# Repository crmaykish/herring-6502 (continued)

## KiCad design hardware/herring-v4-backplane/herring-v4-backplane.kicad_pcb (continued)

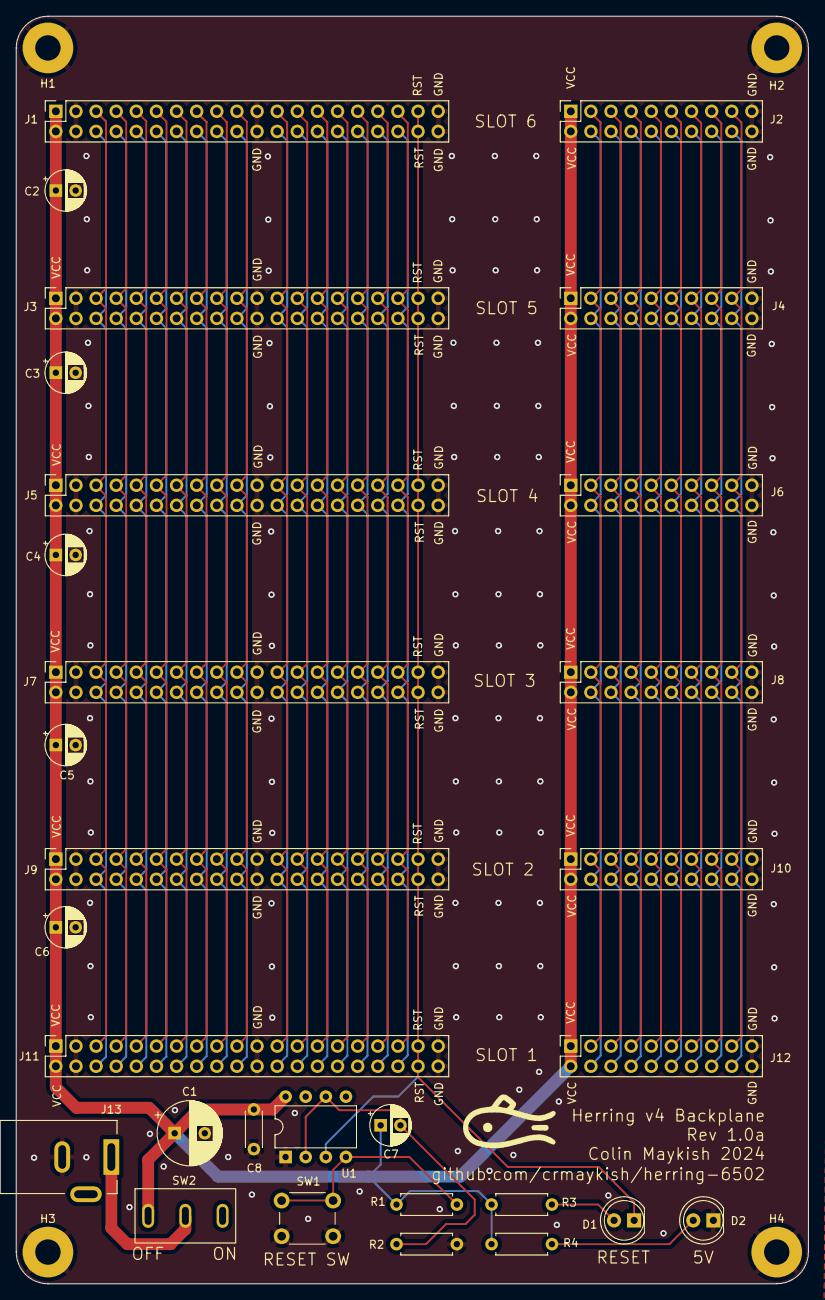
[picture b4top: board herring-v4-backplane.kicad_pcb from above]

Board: 2 copper layers, 100.0 x 160.0 mm, 34 parts (0 on the bottom side), 54 nets.

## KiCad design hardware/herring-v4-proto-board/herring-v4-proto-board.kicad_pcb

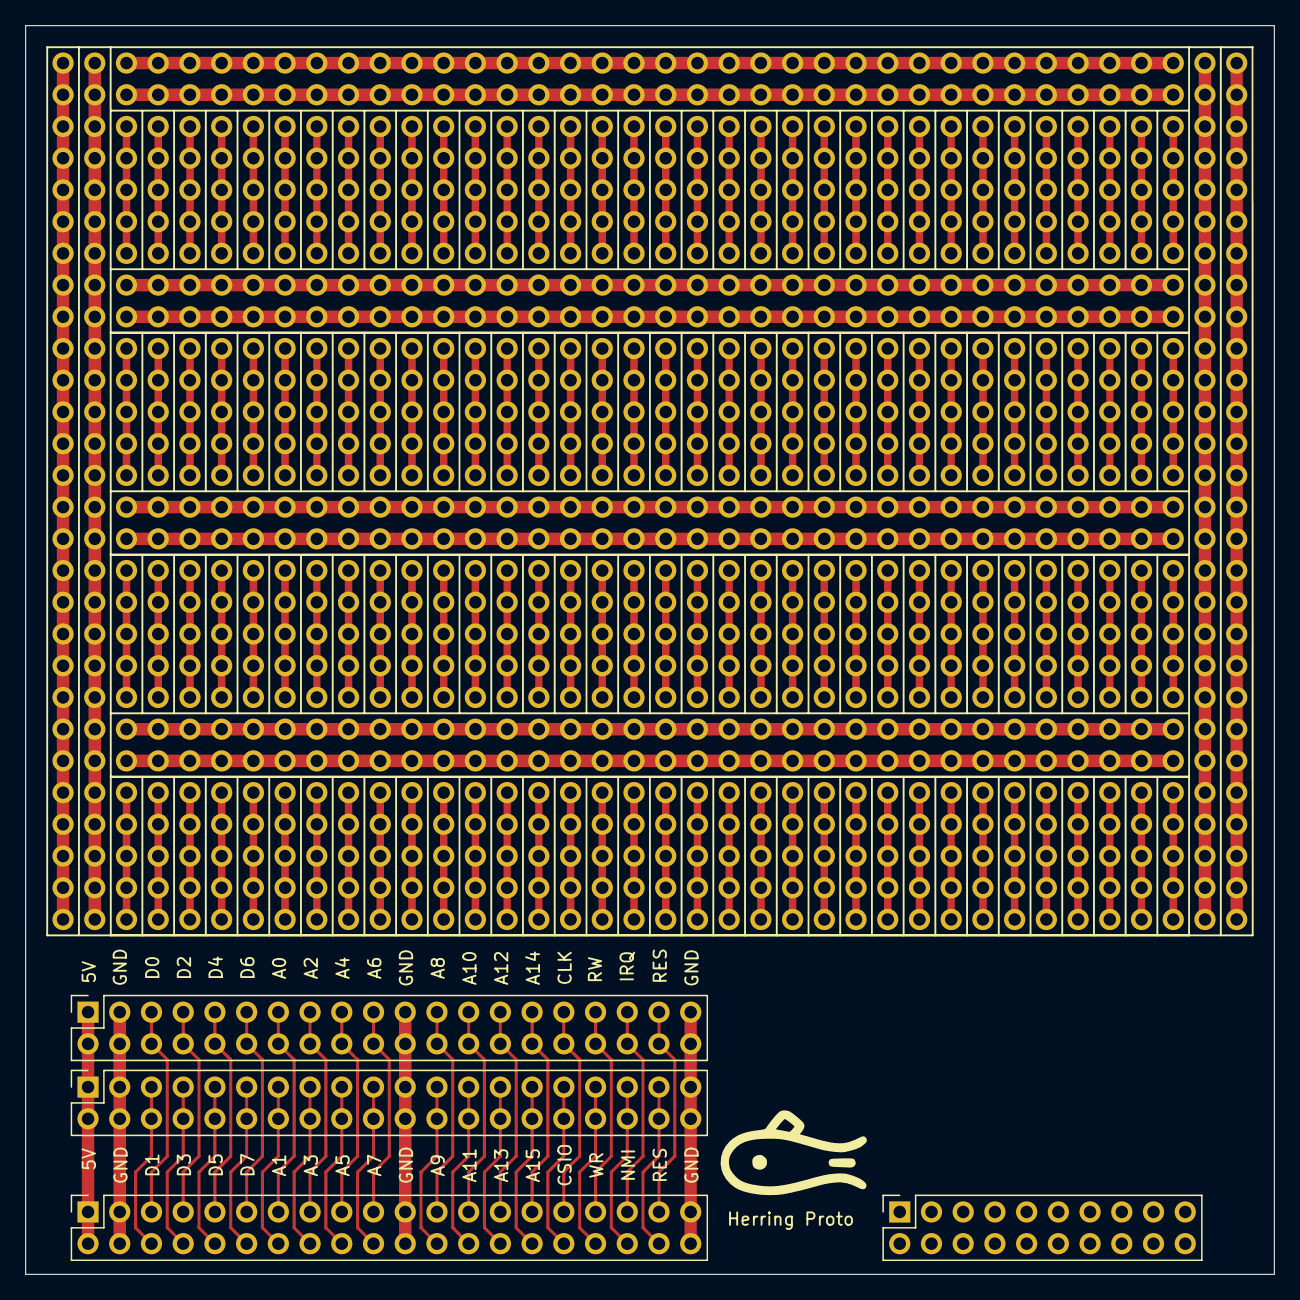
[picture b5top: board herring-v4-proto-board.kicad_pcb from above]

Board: 2 copper layers, 100.0 x 100.0 mm, 4 parts (0 on the bottom side), 33 nets.

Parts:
J1, J4, J5: Conn_02x20_Odd_Even; PinSocket_2x20_P2.54mm_Vertical
J2: Conn_02x10_Odd_Even; PinSocket_2x10_P2.54mm_Vertical

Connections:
+5V: J1.1, J1.2, J4.1, J4.2, J5.1, J5.2
/A0: J1.13, J5.13, J5.14
/A1: J1.14, J4.13, J4.14
/A2: J1.15, J5.15, J5.16
/A3: J1.16, J4.15, J4.16
/A4: J1.17, J5.17, J5.18
/A5: J1.18, J4.17, J4.18
/A6: J1.19, J5.19, J5.20
/A7: J1.20, J4.19, J4.20
/A8: J1.23, J5.23, J5.24
/A9: J1.24, J4.23, J4.24
/A10: J1.25, J5.25, J5.26
/A11: J1.26, J4.25, J4.26
/A12: J1.27, J5.27, J5.28
/A13: J1.28, J4.27, J4.28
/A14: J1.29, J5.29, J5.30
/A15: J1.30, J4.29, J4.30
/CLK: J1.31, J5.31, J5.32
/D0: J1.5, J5.5, J5.6
/D1: J1.6, J4.5, J4.6
/D2: J1.7, J5.7, J5.8
/D3: J1.8, J4.7, J4.8
/D4: J1.9, J5.9, J5.10
/D5: J1.10, J4.9, J4.10
/D6: J1.11, J5.11, J5.12
/D7: J1.12, J4.11, J4.12
//CS_IO: J1.32, J4.31, J4.32
//IRQ: J1.35, J5.35, J5.36
//NMI: J1.36, J4.35, J4.36
//RES: J1.37, J1.38, J4.37, J4.38, J5.37, J5.38
//RW: J1.33, J5.33, J5.34
//WR: J1.34, J4.33, J4.34
GND: J1.3, J1.4, J1.21, J1.22, J1.39, J1.40, J2.19, J2.20, J4.3, J4.4, J4.21, J4.22, J4.39, J4.40, J5.3, J5.4, J5.21, J5.22, J5.39, J5.40

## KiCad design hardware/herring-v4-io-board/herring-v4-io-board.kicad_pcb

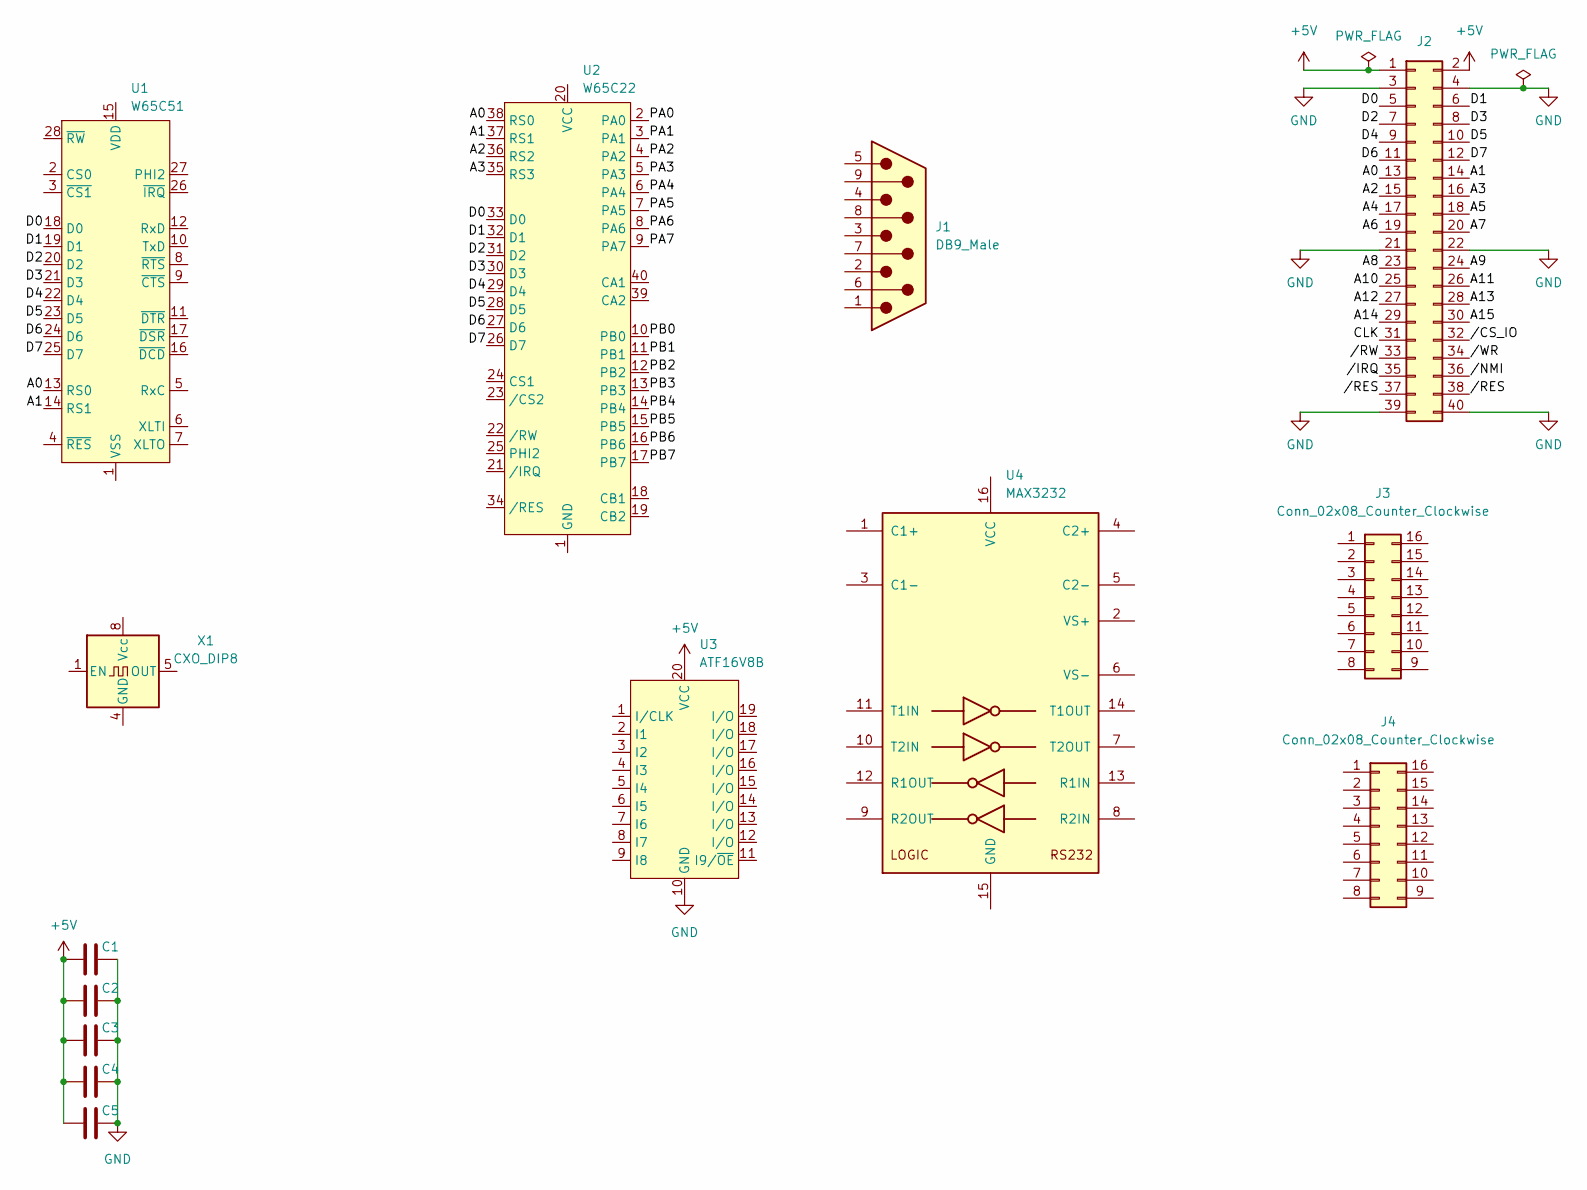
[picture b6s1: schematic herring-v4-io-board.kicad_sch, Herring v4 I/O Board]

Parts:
C1, C2, C3, C4, C5: C; C_Disc_D4.3mm_W1.9mm_P5.00mm
J1: DB9_Male; DSUB-9_Male_Horizontal_P2.77x2.84mm_EdgePinOffset7.70mm_Hou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
J2: Conn_02x20_Odd_Even; PinSocket_2x20_P2.54mm_Vertical
J3, J4: Conn_02x08_Counter_Clockwise; PinSocket_2x08_P2.54mm_Vertical
U1: W65C51; DIP-28_W15.24mm
U2: W65C22; DIP-40_W15.24mm
U3: ATF16V8B; DIP-20_W7.62mm
U4: MAX3232
X1: CXO_DIP8; Oscillator_DIP-8

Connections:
+5V: C1.1, C2.1, C3.1, C4.1, C5.1, J2.1, J2.2, U3.20 (VCC)
/A0: J2.13, U1.13 (RS0), U2.38 (RS0)
/A1: J2.14, U1.14 (RS1), U2.37 (RS1)
/A2: J2.15, U2.36 (RS2)
/A3: J2.16, U2.35 (RS3)
/A4: J2.17
/A5: J2.18
/A6: J2.19
/A7: J2.20
/A8: J2.23
/A9: J2.24
/A10: J2.25
/A11: J2.26
/A12: J2.27
/A13: J2.28
/A14: J2.29
/A15: J2.30
/CLK: J2.31
/D0: J2.5, U1.18 (D0), U2.33 (D0)
/D1: J2.6, U1.19 (D1), U2.32 (D1)
/D2: J2.7, U1.20 (D2), U2.31 (D2)
/D3: J2.8, U1.21 (D3), U2.30 (D3)
/D4: J2.9, U1.22 (D4), U2.29 (D4)
/D5: J2.10, U1.23 (D5), U2.28 (D5)
/D6: J2.11, U1.24 (D6), U2.27 (D6)
/D7: J2.12, U1.25 (D7), U2.26 (D7)
/PA0: U2.2 (PA0)
/PA1: U2.3 (PA1)
/PA2: U2.4 (PA2)
/PA3: U2.5 (PA3)
/PA4: U2.6 (PA4)
/PA5: U2.7 (PA5)
/PA6: U2.8 (PA6)
/PA7: U2.9 (PA7)
/PB0: U2.10 (PB0)
/PB1: U2.11 (PB1)
/PB2: U2.12 (PB2)
/PB3: U2.13 (PB3)
/PB4: U2.14 (PB4)
/PB5: U2.15 (PB5)
/PB6: U2.16 (PB6)
/PB7: U2.17 (PB7)
//CS_IO: J2.32
//IRQ: J2.35
//NMI: J2.36
//RES: J2.37, J2.38
//RW: J2.33
//WR: J2.34
GND: C1.2, C2.2, C3.2, C4.2, C5.2, J2.3, J2.4, J2.21, J2.22, J2.39, J2.40, U3.10 (GND)

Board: 2 copper layers, 14 parts (0 on the bottom side), 15 nets, no tracks yet.

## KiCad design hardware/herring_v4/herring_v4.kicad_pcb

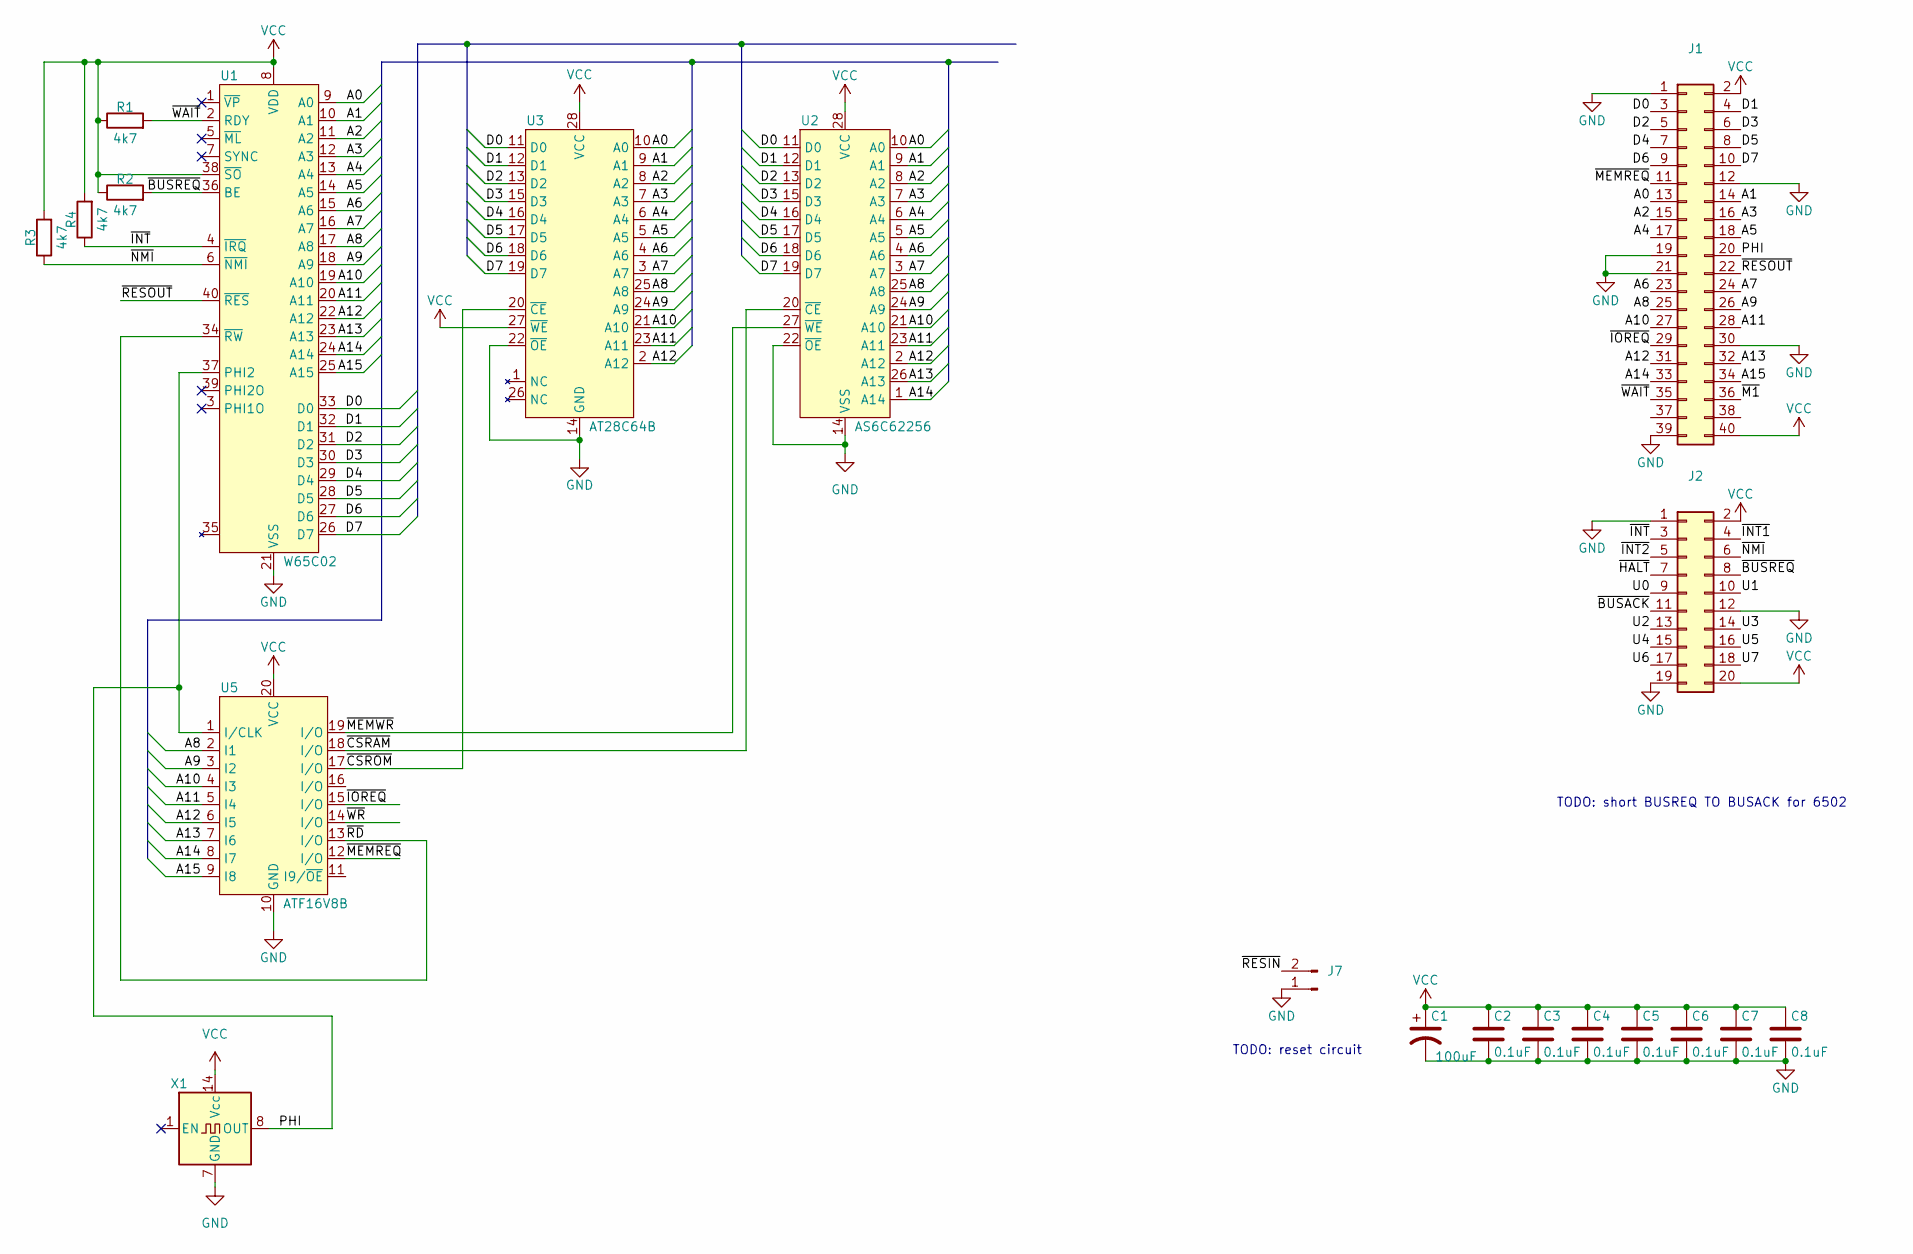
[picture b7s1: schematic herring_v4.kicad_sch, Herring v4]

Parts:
C1: 100uF; CP_Radial_D8.0mm_P3.50mm
C2, C3, C4, C5, C6, C7, C8: 0.1uF; C_Disc_D5.0mm_W2.5mm_P5.00mm
J1: Conn_02x20_Odd_Even; PinSocket_2x21_P2.54mm_Horizontal
J2: Conn_02x10_Odd_Even; PinSocket_2x10_P2.54mm_Horizontal
J7: Conn_01x02_Male; PinHeader_1x02_P2.54mm_Vertical
R1, R2, R3, R4: 4k7; R_Axial_DIN0207_L6.3mm_D2.5mm_P10.16mm_Horizontal
U1: W65C02; DIP-40_W15.24mm_Socket
U2: AS6C62256; DIP-28_W15.24mm_Socket
U3: AT28C64B; DIP-28_W15.24mm_Socket
U5: ATF16V8B; DIP-20_W7.62mm_Socket
X1: CXO_DIP14; Oscillator_DIP-14

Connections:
/A0: J1.13, U1.9 (A0), U2.10 (A0), U3.10 (A0)
/A1: J1.14, U1.10 (A1), U2.9 (A1), U3.9 (A1)
/A2: J1.15, U1.11 (A2), U2.8 (A2), U3.8 (A2)
/A3: J1.16, U1.12 (A3), U2.7 (A3), U3.7 (A3)
/A4: J1.17, U1.13 (A4), U2.6 (A4), U3.6 (A4)
/A5: J1.18, U1.14 (A5), U2.5 (A5), U3.5 (A5)
/A6: J1.23, U1.15 (A6), U2.4 (A6), U3.4 (A6)
/A7: J1.24, U1.16 (A7), U2.3 (A7), U3.3 (A7)
/A8: J1.25, U1.17 (A8), U2.25 (A8), U3.25 (A8), U5.2 (I1)
/A9: J1.26, U1.18 (A9), U2.24 (A9), U3.24 (A9), U5.3 (I2)
/A10: J1.27, U1.19 (A10), U2.21 (A10), U3.21 (A10), U5.4 (I3)
/A11: J1.28, U1.20 (A11), U2.23 (A11), U3.23 (A11), U5.5 (I4)
/A12: J1.31, U1.22 (A12), U2.2 (A12), U3.2 (A12), U5.6 (I5)
/A13: J1.32, U1.23 (A13), U2.26 (A13), U5.7 (I6)
/A14: J1.33, U1.24 (A14), U2.1 (A14), U5.8 (I7)
/A15: J1.34, U1.25 (A15), U5.9 (I8)
/D0: J1.3, U1.33 (D0), U2.11 (D0), U3.11 (D0)
/D1: J1.4, U1.32 (D1), U2.12 (D1), U3.12 (D1)
/D2: J1.5, U1.31 (D2), U2.13 (D2), U3.13 (D2)
/D3: J1.6, U1.30 (D3), U2.15 (D3), U3.15 (D3)
/D4: J1.7, U1.29 (D4), U2.16 (D4), U3.16 (D4)
/D5: J1.8, U1.28 (D5), U2.17 (D5), U3.17 (D5)
/D6: J1.9, U1.27 (D6), U2.18 (D6), U3.18 (D6)
/D7: J1.10, U1.26 (D7), U2.19 (D7), U3.19 (D7)
/PHI: J1.20, U1.37 (PHI2), U5.1 (I/CLK), X1.8 (OUT)
/U0: J2.9
/U1: J2.10
/U2: J2.13
/U3: J2.14
/U4: J2.15
/U5: J2.16
/U6: J2.17
/U7: J2.18
/~BUSACK: J2.11
/~BUSREQ: J2.8, R2.2, U1.36 (BE)
/~CSRAM: U2.20 (~CE), U5.18 (I/O)
/~CSROM: U3.20 (~CE), U5.17 (I/O)
/~HALT: J2.7
/~INT1: J2.4
/~INT2: J2.5
/~INT: J2.3, R4.1, U1.4 (~IRQ)
/~IOREQ: J1.29, U5.15 (I/O)
/~M1: J1.36
/~MEMREQ: J1.11, U5.12 (I/O)
/~MEMWR: U2.27 (~WE), U5.19 (I/O)
/~NMI: J2.6, R3.1, U1.6 (~NMI)
/~RD: U1.34 (~RW), U5.13 (I/O)
/~RESIN: J7.2
/~RESOUT: J1.22, U1.40 (~RES)
/~WAIT: J1.35, R1.2, U1.2 (RDY)
/~WR: U5.14 (I/O)
GND: C1.2, C2.2, C3.2, C4.2, C5.2, C6.2, C7.2, C8.2, J1.1, J1.12, J1.19, J1.21, J1.30, J1.39, J2.1, J2.12, J2.19, J7.1, U1.21 (VSS), U2.14 (VSS), U2.22 (~OE), U3.14 (GND), U3.22 (~OE), U5.10 (GND), X1.7 (GND)
VCC: C1.1, C2.1, C3.1, C4.1, C5.1, C6.1, C7.1, C8.1, J1.2, J1.40, J2.2, J2.20, R1.1, R2.1, R3.2, R4.2, U1.8 (VDD), U1.38 (~SO), U2.28 (VCC), U3.27 (~WE), U3.28 (VCC), U5.20 (VCC), X1.14 (Vcc)

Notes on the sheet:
TODO: short BUSREQ TO BUSACK for 6502
TODO: reset circuit

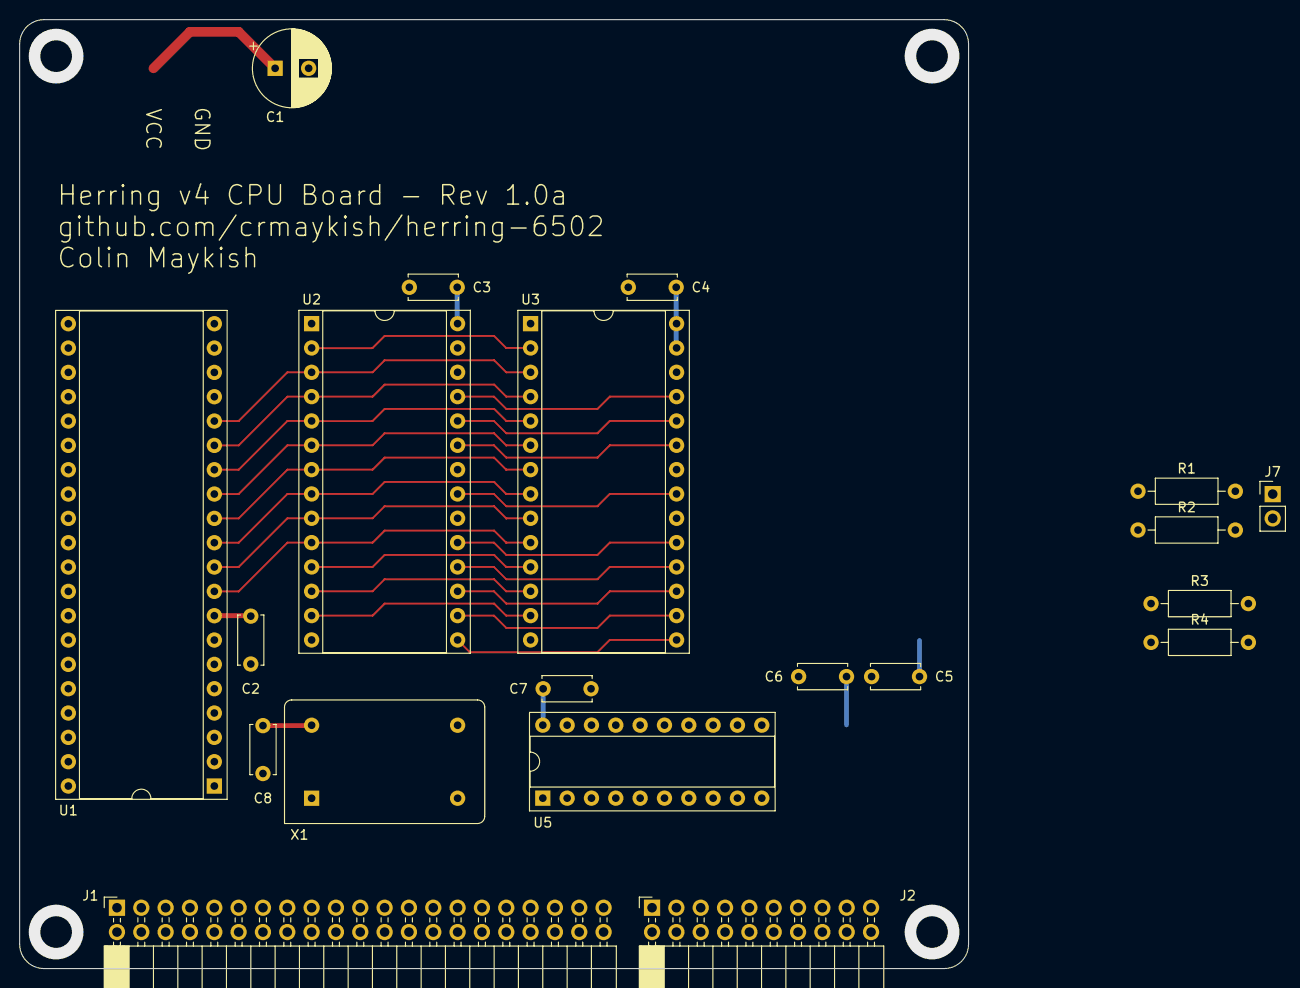
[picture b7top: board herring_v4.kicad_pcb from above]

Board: 2 copper layers, 99.1 x 99.1 mm, 20 parts (0 on the bottom side), 38 nets.

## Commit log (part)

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2021-06-08 Added Arduino monitor sketch and LED panel controller
2021-06-08 defined arduino pinout
2021-06-11 ASM demos and GPU emulator firmware
2021-06-12 monitor working with cpu daughter board
2021-06-12 formatting
2021-06-12 Added logo
2021-06-13 RAM test assembly code running correctly
2021-06-14 updated memory map
2021-06-16 Port A on the VIA board hooked up and working correctly
2021-06-16 VIA and LCD proof of concept
2021-06-16 better clock control
2021-06-16 default to CPU running
2021-06-17 prep monitor program for uart emulation
2021-06-17 fake uart sort of working, not worth the effort
2021-06-17 start converting LCD test to 128x64
2021-06-17 Emulated UART only works up to a few kHz CPU speed before it can no longer keep up
2021-06-17 hacking uart reads
2021-06-18 cleanup
2021-06-22 watching all control pins
2021-06-22 refactored bus monitor
2021-06-22 minor errors from refactor fixed
2021-06-22 graphic display not working
2021-06-25 ROM test passed
2021-06-25 RAM test working
2021-06-25 LCD test is working
2021-06-25 build script cleanup
2021-06-29 crude SD card features added to monitor
2021-06-29 basic read and write ram functions
2021-06-29 Add bus enable pin control
2021-06-29 Messing with RAM writing...
2021-07-02 ASM cleanup
2021-07-02 fixed asm demos for board 1
2021-07-04 Converted to CC65 assembler
2021-07-04 C code compiling
2021-07-04 acia c code compiles
2021-07-05 VIA demo with CA65
2021-07-05 static vars
2021-07-05 move VIA code to C
2021-07-05 gitignore
2021-07-06 outline of a command/response terminal for monitor
2021-07-07 refactored ACIA code to new file
2021-07-07 Rebuilt the cc65 library from sim6502. stdlib calls all seem to work now
2021-07-07 Change default clock speed to 50 KHz
2021-07-08 print and goto commands in BASIC are implemented
2021-07-08 Add explicit length checks to BASIC command parsing
2021-07-08 Added peek and poke commands
2021-07-09 refactored for new memory board
2021-07-10 everything sucks
2021-07-10 better speeds and breaks
2021-07-10 serial port seems to be working with PCBs
2021-07-11 start over on firmware
2021-07-11 interactive command prompt shell in ASM
2021-07-11 start over with C
2021-07-12 Code loaded into RAM and running
2021-07-12 Loading program data over serial port
2021-07-12 Installed clock board, running loader at 1MHz
2021-07-12 cc65 config for RAM loaded programs
2021-07-12 system monitor stubbed out
2021-07-12 memdump style command running
2021-07-12 primes demo
2021-07-13 fixed memdump command
2021-07-13 increase serial baudrate to 19200
2021-07-13 clean common build artifacts from either sub dir
2021-07-13 Fixed makefile issue causing C files to built for default target architecture
2021-07-14 added loading bar to serial transfer script
2021-07-14 peek works with any size hex input
2021-07-15 Added poke and reset, reload commands to sysmon
2021-07-15 Added ASCII printout to memdump
2021-07-15 proof of concept LED matrix connection with VIA
2021-07-16 SPI not working
2021-07-16 memdump improvements
2021-07-17 started an SD interface on the atmega4809
2021-07-18 fancy logo in the system monitor
2021-07-18 update sysmon
2021-07-18 Started work on AVR clock control
2021-07-21 SD card init successful
2021-07-21 Reading first block from SD card
2021-07-21 reading first sector of SD card and decoding partition info
2021-07-22 trim a bunch of dead weight and reorganize a bit
2021-07-22 Compile time feature flags in sysmon
2021-07-22 sysmon cleanup
2021-07-23 counter cleanup
2021-07-24 more fun counter program
2021-07-24 Added BASIC library and PC front-end:
2021-07-24 comments
2021-07-24 Board B proof of concept in C
2021-07-25 snprintf working on 65c02
2021-07-25 Cleaned up print function
2021-07-25 Refactored serial is working at low speed, not 1MHz
2021-07-25 Cleanup old code
2021-07-26 basic loader logic implemented
2021-07-26 build scripts for loader and ram programs
2021-07-27 a bunch of crap
2021-07-28 Back to booting with a C config
2021-07-28 putc working at 2Mhz
2021-07-28 ACIA print function in ASM
2021-07-29 Clock controller runs, stops, and single steps
2021-07-30 Turn the clock to INPUT when not being used
2021-07-31 Add ACIA fix for WDC65C51 bug
2021-07-31 Serial loader working again.. WDC chips are terrible
2021-07-31 Add option to zero program RAM
2021-07-31 Added readline and better memdump
2021-07-31 started work on disassembler
2021-08-01 Add memtest command
2021-08-01 Disassembling some basic opcodes
2021-08-02 Really basic text editing
2021-08-03 First self-assembled code runs
2021-08-04 Line 2 on LCD display
2021-08-05 LCD module handles text wrapping and resetting correctly
2021-08-05 Handle carriage return in lcd_write()
2021-08-05 cross-assembler stubbed out
2021-08-05 Assembler works on Herring
2021-08-05 Fixed disassemble command
2021-08-09 fixed crash from EOF character in source
2021-08-09 remove printfs from assembler
2021-08-09 Added support for .org and stx/sty
2021-08-09 remove binary
2021-08-10 hexdump
2021-08-11 ANSI stuff kind of works
2021-08-17 memulator stub
2021-08-18 basic primes finder
2021-08-19 proof of concept memory emulator
2021-08-19 add VIA to memulator
2021-08-22 Serial demo with memulator installed
2021-08-22 Add second core for serial comms
2021-08-23 fix decoder project files
2021-08-25 Add new RAM to Zero config
2021-08-27 Herring Zero test assembly
2021-08-27 ATMEGA4809 monitor stubbed out
2021-08-28 ROM emulator loading code over serial
2021-08-28 Bump clock to 50KHz
2021-08-28 move memulator
2021-08-28 Set CPU clock to 2 MHz
2021-08-28 Clean up old projects and ccode
2021-08-28 Add screen clear
2021-08-28 Add peek, poke, and memdump to monitor program
2021-08-29 Add help, jump, and zero commands to Zero Mon
2021-08-29 Add clear command to Zero Mon
2021-08-29 Set clock speed to 1 MHz
2021-09-01 Fix free command
2021-09-02 Add description of monitor program to README
2021-09-02 Added run-from-ram config and load command to serial monitor
2021-09-10 proof of concept GPIO latch working on Upduino board
2021-09-10 Add decoder 3 and 4 outputs
2021-09-10 Add demo program for FPGA GPIO latch
2021-09-10 Add low voltage ROM and increase CPU speed to 6.25 MHz
2021-09-12 Set clock to 3.33 Mhz
2021-09-12 proof of concept VGA signal on FPGA
2021-09-12 drawing rectangles demo
2021-09-12 proof of concept drawing pixels from framebuffer
2021-09-14 Simple CPU interface to the VGA controller
2021-09-15 simple pixel movement demo
2021-09-15 Increase VGA resolution to 800x600
2021-09-17 fpga pinouts
2021-09-17 refactor address decoder
2021-09-17 Finished up address decoder refactoring
2021-09-18 Stripped down VGA timings
2021-09-18 Add framebuffer module
2021-09-18 VGA module back to working state
2021-09-18 Fixed the -14 CPU clock issues, just use PHI2 for everything
2021-09-19 decoder project files
2021-09-19 back to 160x120
2021-09-20 fixed clear command
2021-09-21 Add some test benches
2021-09-25 Simple LCD C API
2021-09-25 LCD printing works
2021-09-28 LCD stuff
2021-11-16 Demo pattern
2021-11-17 simple sprite drawing
2021-11-17 Basic character fonts and screen buffer working
2021-11-17 fixed font and framebuffer loading
2021-11-18 bigger framebuffer cells working with new version of apio
2021-11-18 reading ascii from the data bus
2021-11-18 serial to VGA text demo
2021-11-18 More font characters
2021-11-19 Two versions of the GPU working
2021-11-19 cleanup old projects
2021-11-19 Added double buffering at 80x60 resolution
2021-11-19 Configurable framebuffer size
2021-11-19 Randomized bouncing cubes demo
2021-11-19 Remove old file
2021-11-19 Stubbed out basic demo for test mode GPU
2021-11-21 Using PLL to generate pixel clock
2021-11-21 Create a framebuffer API header
2021-11-21 crappy line drawing
2021-11-22 Comment fixes in textmode GPU
2021-11-22 Building Pi Pico code in a Docker container
2021-12-01 New FPGA pin mapping for GPU
2021-12-01 Decrease framebuffer size
2021-12-01 Add CPU type to monitor splash screen
2021-12-02 Added PLD file for GAL version of address decoder
2021-12-05 Remove old unused demos and tools
2021-12-05 Remove loader lib from git tracking
2021-12-05 Simpler structure for the firmware code
2021-12-06 Removed old assembler
2021-12-06 Cleanup unused ASM defs
2021-12-06 Small improvements to the command parsing in Herring Monitor
2021-12-06 More include cleanup
2021-12-07 Generalized handling of input commands in Herring Monitor
2021-12-07 Fixed bug in the help message for param2
2021-12-07 Added command descriptions to help message and added clear screen command
2021-12-07 Implented backspace in Herring Monitor
2021-12-08 Readline improvements
2021-12-08 Fixed GAL logic for LCD display
2021-12-08 LCD Display working again
2021-12-09 Increased serial baudrate to 115200
2021-12-11 remove lib files from git
2021-12-11 Cleaned up config for RAM based programs
2021-12-11 faster primes
2021-12-11 more terminal colors
2021-12-11 Fixed conway neighbor counting
2021-12-14 Add chip8 code
2021-12-14 CHIP-8 emulator is mostly working on Herring terminal
2021-12-14 Add CHIP-8 project as a git submodule
2021-12-16 Add additional address pins to GAL
2021-12-19 Using serial input polling for CHIP-8 emulator
2021-12-20 Updated CHIP-8 library
2021-12-20 Update CHIP-8 emulator to use screen clear function
2021-12-21 Updated address decoding for v1.5
2021-12-21 Cleaned up Conway and removed serial trasfer script
2021-12-21 Remove the weird start byte check from serial loader firmware
2021-12-21 Moved firmware builds to a Makefile
2021-12-21 Updated readme and v1.5 build
2021-12-21 Fixed some typos in README
2021-12-22 Game of life back up and running
2021-12-22 CHIP-8 emulator running again
2021-12-22 Game of Life runs until stopped
2021-12-22 Echo bytes read when loading from serial port
2021-12-22 remove conway infinite loop
2021-12-22 make sure RAM firmware is clearing BSS
2021-12-22 Reading file contents from USB drive over serial
2022-01-24 Implemented write(), printf is now working
2022-01-25 Reading file data from parallel USB interface
2022-01-26 Implement VIA timers for delay function
2022-01-26 Reading large files from USB drive
2022-01-26 Read USB files into RAM
2022-01-26 USB controller is flaky
2022-01-26 Update USB registers
2022-01-27 reading multiple parts
2022-01-27 Reading files of arbitrary size continuously over serial
2022-01-27 Added file list function
2022-02-11 Add v3 address decoder GAL
2022-08-11 Created GAL logic for v2 boards
2022-08-18 Working demos for framebuffer and textmode graphics
2022-08-18 Added more font characters and conway VGA demo
2022-08-19 Added font color to VGA text mode
2022-08-20 reading block data from SD card
2022-08-20 Moved SPI code into library
2022-08-20 Moved SD code to its own file
2022-08-21 Stubbed out assembler
2022-08-21 Moved SD card circuit to dedicated VIA board
2022-08-29 v3 gal
2022-10-17 Move PLD code to new directory
2022-10-18 Start KiCAD project for Herring v4
2022-10-18 Add 16C550 symbol
2022-10-19 Created KiCAD symbols for core components
2022-11-03 Replace 65C51 with 16C550
2022-11-03 Add 16C550 to schematic
2022-11-03 Strip down CPU board schematic
2024-06-03 Dust off the single PCB version of Herring and boot it back up
2024-07-12 Core board and backplane for v4 routed
2024-07-12 stubbed out I/O board
2024-07-13 herring v4 backplane routed
2024-07-14 Add logos to backplane
2024-07-27 Herring v4 backplane gerber files
2024-07-28 CPU board schematic mostly done, started routing
2024-07-30 Routed buffers and expansion header
2024-08-01 Stub out v4 ACIA board
2024-08-05 Add KiCAD renders
2024-08-21 Wipe v4
2026-06-16 Set the cc65 lib dir dynamically
2026-06-17 Remove CH376 code
2026-06-19 Herring-F: Clear out old PLD logic
2026-06-19 Herring-F: Strip existing firmware down to basic monitor + conway demo
2026-06-19 Herring-F: Set up ROM and GPIO register
2026-06-19 Herring-F: 32KB of fixed RAM
2026-06-22 Herring-F: Port back to Nano 9k
2026-06-22 Herring-F: 6551 ACIA bringup
2026-06-22 Herring-F: Manual reset button
